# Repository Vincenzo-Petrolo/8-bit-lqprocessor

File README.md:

# 8-bit-lqprocessor
My build of a 8 bit low quality custom processor

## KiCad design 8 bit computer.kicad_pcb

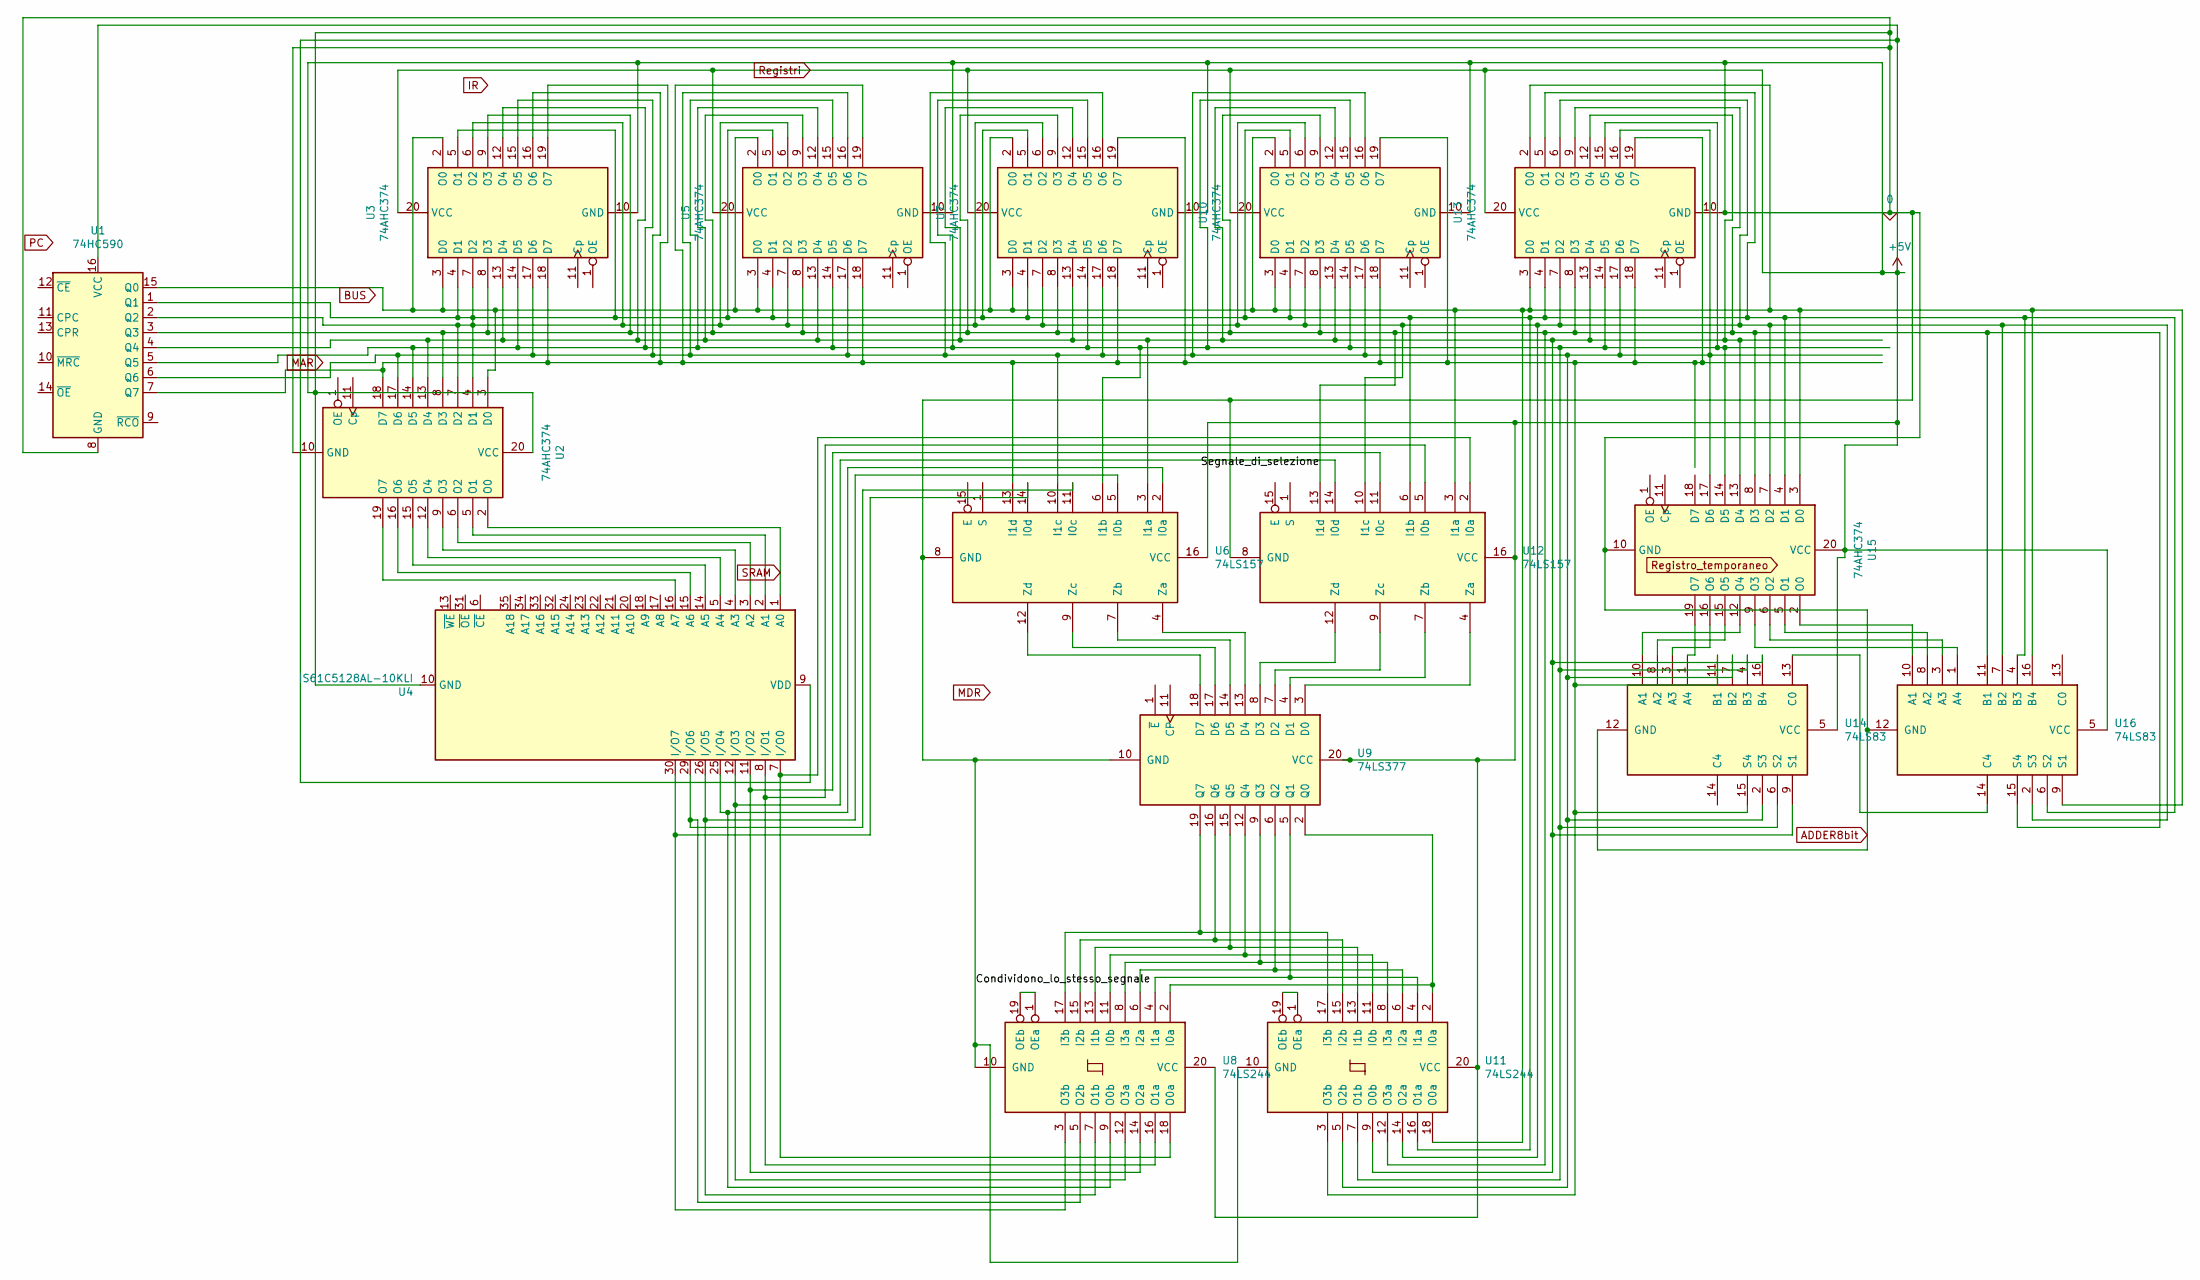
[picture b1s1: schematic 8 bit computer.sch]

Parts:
U1: 74HC590; QSOP-16_3.9x4.9mm_P0.635mm
U2, U3, U5, U7, U10, U13, U15: 74AHC374; QSOP-20_3.9x8.7mm_P0.635mm
U4: IS61C5128AL-10KLI; SOJ-36_10.16x23.49mm_P1.27mm
U6: 74LS157; QSOP-16_3.9x4.9mm_P0.635mm
U8, U11: 74LS244; QSOP-20_3.9x8.7mm_P0.635mm
U9: 74LS377; QSOP-20_3.9x8.7mm_P0.635mm
U12: 74LS157; MSOP-16_3x4mm_P0.5mm
U14, U16: 74LS83; MSOP-16_3x4mm_P0.5mm

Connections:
ADDER8bit: U1.8 (GND), U1.16 (VCC), U2.10 (GND), U2.20 (VCC), U3.10 (GND), U3.20 (VCC), U4.9 (VDD), U4.10 (GND), U4.27 (VDD), U4.28 (GND), U5.10 (GND), U5.20 (VCC), U6.8 (GND), U6.16 (VCC), U7.10 (GND), U7.20 (VCC), U8.10 (GND), U8.20 (VCC), U9.10 (GND), U9.20 (VCC), U10.10 (GND), U10.20 (VCC), U11.10 (GND), U11.20 (VCC), U12.8 (GND), U12.16 (VCC), U13.10 (GND), U13.20 (VCC), U14.5 (VCC), U14.12 (GND), U15.10 (GND), U15.20 (VCC), U16.5 (VCC), U16.12 (GND)
unnamed: U1.1 (Q1), U1.2 (Q2), U2.4 (D1), U2.7 (D2), U3.4 (D1), U3.5 (O1), U3.6 (O2), U3.7 (D2), U5.4 (D1), U5.5 (O1), U5.6 (O2), U5.7 (D2), U7.4 (D1), U7.5 (O1), U7.6 (O2), U7.7 (D2), U10.4 (D1), U10.5 (O1), U10.6 (O2), U10.7 (D2), U11.14 (O2a), U11.16 (O1a), U12.6 (I1b), U12.10 (I1c), U13.4 (D1), U13.5 (O1), U13.6 (O2), U13.7 (D2), U15.4 (D1), U15.7 (D2), U16.2 (S3), U16.4 (B3), U16.6 (S2), U16.7 (B2)
unnamed: U1.3 (Q3), U2.8 (D3), U3.8 (D3), U3.9 (O3), U5.8 (D3), U5.9 (O3), U7.8 (D3), U7.9 (O3), U10.8 (D3), U10.9 (O3), U11.12 (O3a), U12.13 (I1d), U13.8 (D3), U13.9 (O3), U15.8 (D3), U16.11 (B1), U16.15 (S4)
unnamed: U1.4 (Q4), U2.13 (D4), U3.12 (O4), U3.13 (D4), U5.12 (O4), U5.13 (D4), U6.3 (I1a), U7.12 (O4), U7.13 (D4), U10.12 (O4), U10.13 (D4), U11.9 (O0b), U13.12 (O4), U13.13 (D4), U14.9 (S1), U14.16 (B4), U15.13 (D4)
unnamed: U1.5 (Q5), U2.14 (D5), U3.14 (D5), U3.15 (O5), U5.14 (D5), U5.15 (O5), U6.6 (I1b), U7.14 (D5), U7.15 (O5), U10.14 (D5), U10.15 (O5), U11.7 (O1b), U13.14 (D5), U13.15 (O5), U14.4 (B3), U14.6 (S2), U15.14 (D5)
unnamed: U1.6 (Q6), U2.17 (D6), U3.16 (O6), U3.17 (D6), U5.16 (O6), U5.17 (D6), U6.10 (I1c), U7.16 (O6), U7.17 (D6), U10.16 (O6), U10.17 (D6), U11.5 (O2b), U13.16 (O6), U13.17 (D6), U14.2 (S3), U14.7 (B2), U15.17 (D6)
unnamed: U1.7 (Q7), U2.18 (D7), U3.18 (D7), U3.19 (O7), U5.18 (D7), U5.19 (O7), U6.13 (I1d), U7.18 (D7), U7.19 (O7), U10.18 (D7), U10.19 (O7), U11.3 (O3b), U13.18 (D7), U13.19 (O7), U14.11 (B1), U14.15 (S4)
unnamed: U1.15 (Q0), U2.3 (D0), U3.2 (O0), U3.3 (D0), U5.2 (O0), U5.3 (D0), U7.2 (O0), U7.3 (D0), U10.2 (O0), U10.3 (D0), U11.18 (O0a), U12.3 (I1a), U13.2 (O0), U13.3 (D0), U15.3 (D0), U16.9 (S1), U16.16 (B4)
unnamed: U2.5 (O1), U4.2 (A1)
unnamed: U2.6 (O2), U4.3 (A2)
unnamed: U2.9 (O3), U4.4 (A3)
unnamed: U2.12 (O4), U4.5 (A4)
unnamed: U2.15 (O5), U4.14 (A5)
unnamed: U2.16 (O6), U4.15 (A6)
unnamed: U2.19 (O7), U4.16 (A7)
unnamed: U4.25 (I/O4), U6.2 (I0a), U8.9 (O0b)
unnamed: U4.26 (I/O5), U6.5 (I0b), U8.7 (O1b)
unnamed: U4.29 (I/O6), U6.11 (I0c), U8.5 (O2b)
unnamed: U4.30 (I/O7), U6.14 (I0d), U8.3 (O3b)
unnamed: U6.4 (Za), U9.13 (D4)
unnamed: U6.7 (Zb), U9.14 (D5)
unnamed: U6.9 (Zc), U9.17 (D6)
unnamed: U6.12 (Zd), U9.18 (D7)
unnamed: U8.1 (OEa), U8.19 (OEb)
unnamed: U11.1 (OEa), U11.19 (OEb)
unnamed: U8.2 (I0a), U9.2 (Q0), U11.2 (I0a)
unnamed: U8.4 (I1a), U9.5 (Q1), U11.4 (I1a)
unnamed: U8.6 (I2a), U9.6 (Q2), U11.6 (I2a)
unnamed: U8.8 (I3a), U9.9 (Q3), U11.8 (I3a)
unnamed: U8.11 (I0b), U9.12 (Q4), U11.11 (I0b)
unnamed: U8.13 (I1b), U9.15 (Q5), U11.13 (I1b)
unnamed: U8.15 (I2b), U9.16 (Q6), U11.15 (I2b)
unnamed: U8.17 (I3b), U9.19 (Q7), U11.17 (I3b)
unnamed: U4.7 (I/O0), U8.18 (O0a), U12.2 (I0a)
unnamed: U9.3 (D0), U12.4 (Za)
unnamed: U4.8 (I/O1), U8.16 (O1a), U12.5 (I0b)
unnamed: U9.4 (D1), U12.7 (Zb)
unnamed: U9.7 (D2), U12.9 (Zc)
unnamed: U4.11 (I/O2), U8.14 (O2a), U12.11 (I0c)
unnamed: U9.8 (D3), U12.12 (Zd)
unnamed: U4.12 (I/O3), U8.12 (O3a), U12.14 (I0d)
unnamed: U14.1 (A4), U15.19 (O7)
unnamed: U14.3 (A3), U15.16 (O6)
unnamed: U14.8 (A2), U15.15 (O5)
unnamed: U14.10 (A1), U15.12 (O4)
unnamed: U14.13 (C0), U16.14 (C4)
unnamed: U15.2 (O0), U16.10 (A1)
unnamed: U15.5 (O1), U16.8 (A2)
unnamed: U15.6 (O2), U16.3 (A3)
unnamed: U15.9 (O3), U16.1 (A4)
SRAM: U2.2 (O0), U4.1 (A0)

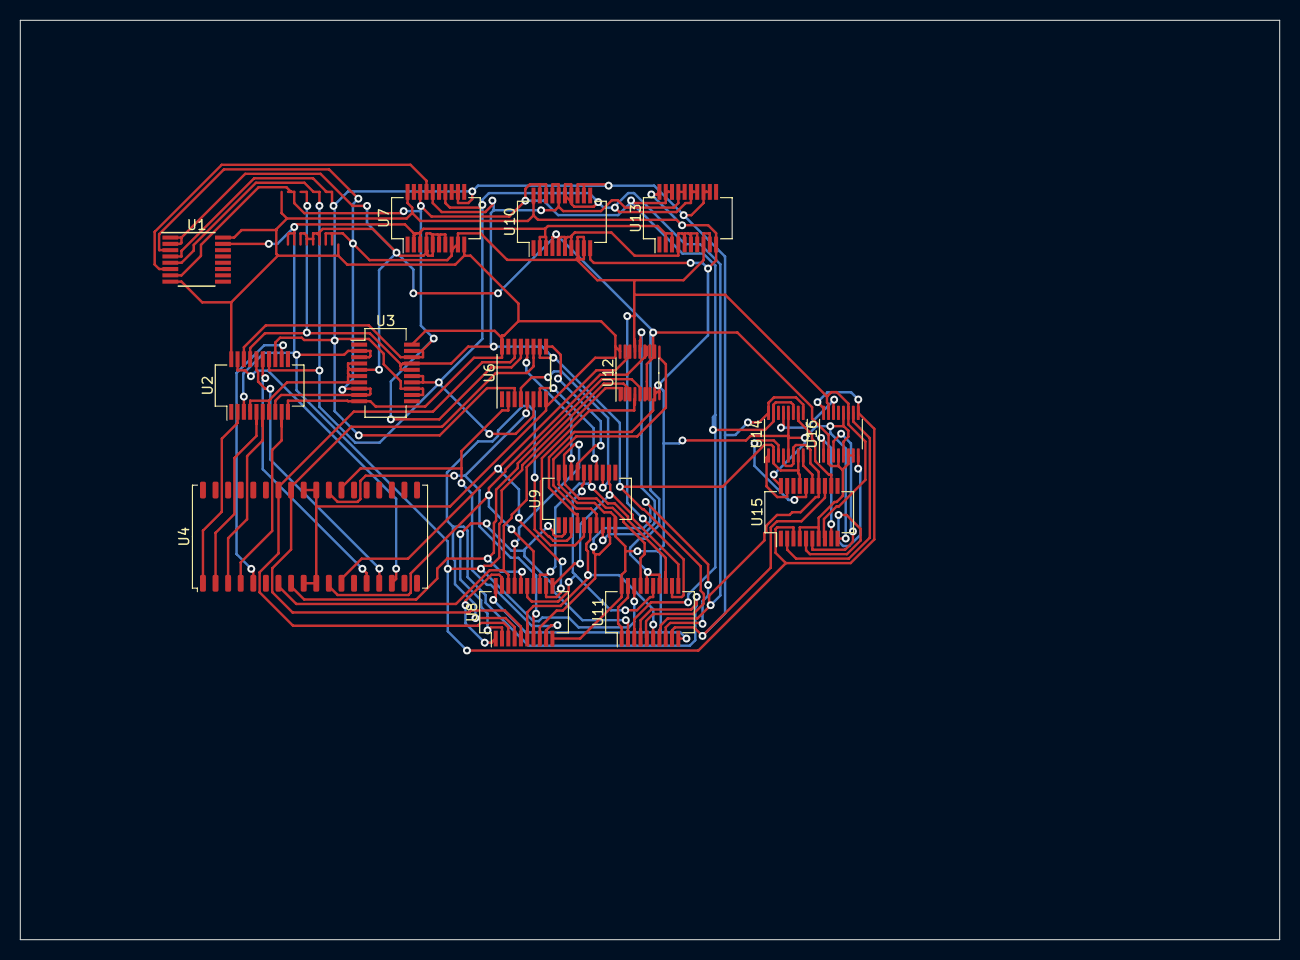
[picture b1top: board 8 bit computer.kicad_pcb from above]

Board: 2 copper layers, 127.0 x 92.7 mm, 15 parts (0 on the bottom side), 51 nets.

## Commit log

2020-09-21 Add : Added branch with assembler files
2020-09-21 Add : First version of processor
2020-09-21 Add : removed unusued branches
